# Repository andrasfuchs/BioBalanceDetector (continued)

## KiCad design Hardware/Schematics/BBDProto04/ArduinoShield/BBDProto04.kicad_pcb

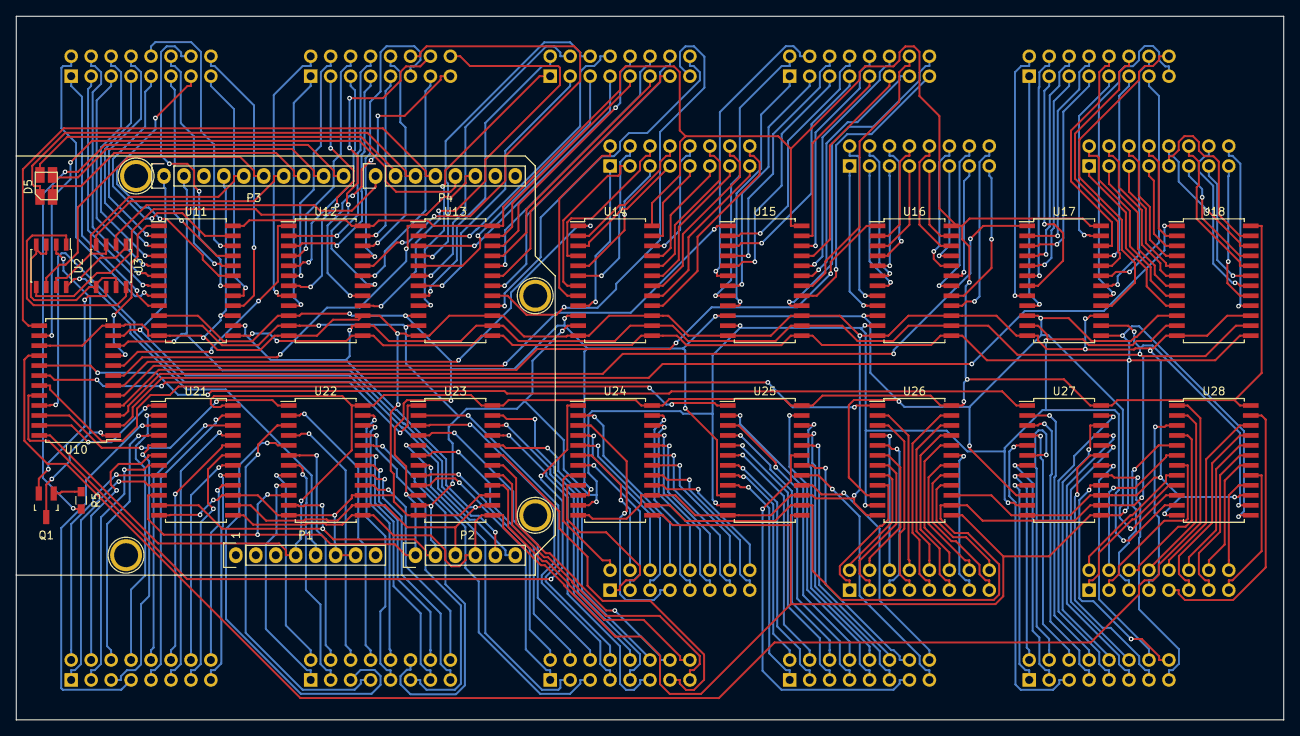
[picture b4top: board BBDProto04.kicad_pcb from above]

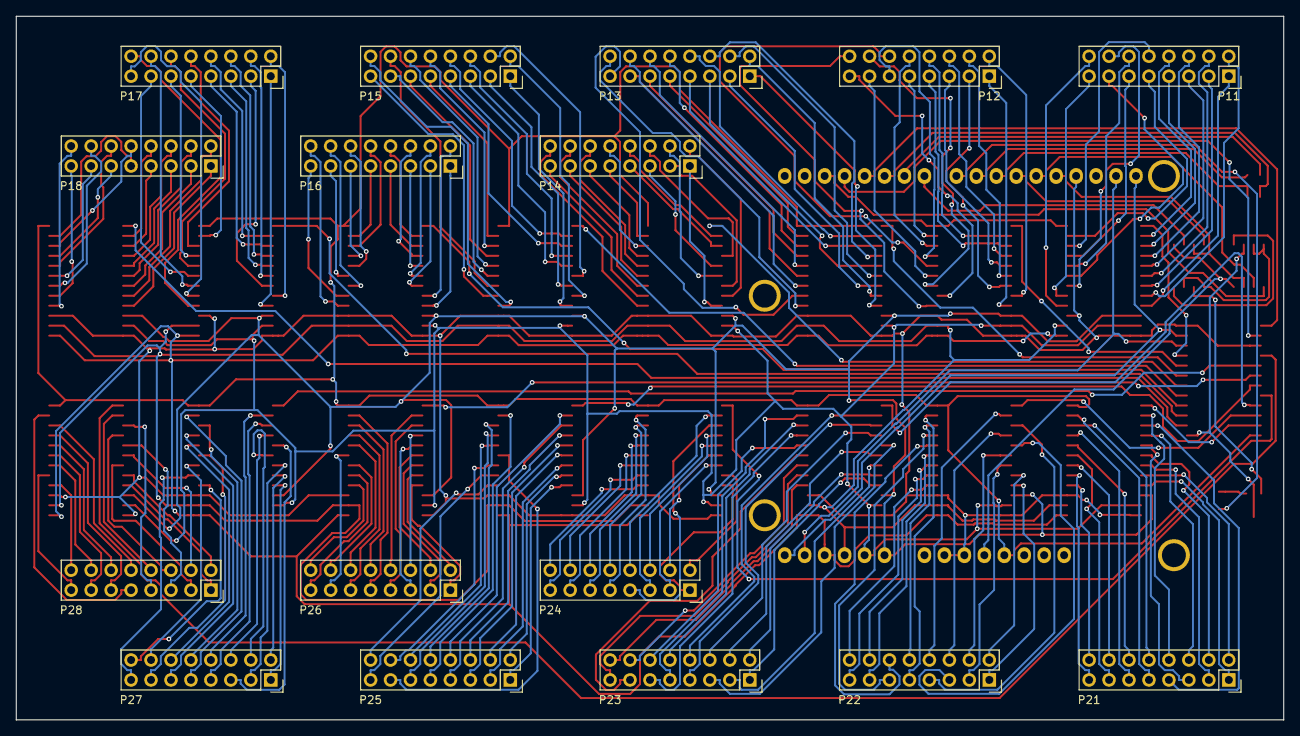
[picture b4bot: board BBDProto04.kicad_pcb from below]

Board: 2 copper layers, 161.3 x 89.5 mm, 46 parts (16 on the bottom side), 298 nets.

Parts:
D5: LED_RCBG; LED_3528-PLCC4
P1: Power; Socket_Strip_Arduino_1x08
P2: Analog; Socket_Strip_Arduino_1x06
P3: Digital; Socket_Strip_Arduino_1x10
P4: Digital; Socket_Strip_Arduino_1x08
P5, P6, P7, P8: CONN_1; Arduino_1pin
P11, P12, P13, P14, P15, P16, P17, P18, P21, P22, P23, P24, P25, P26, P27, P28: CONN_02X08; Socket_Strip_Straight_2x08
Q1: Q_NPN_BCE; SOT-23_Handsoldering
R5: 1k; R_0603_HandSoldering
U2: LTC1864; SOIC-8_3.9x4.9mm_Pitch1.27mm
U3: MCP4822; SOIC-8_3.9x4.9mm_Pitch1.27mm
U10, U11, U12, U13, U14, U15, U16, U17, U18, U21, U22, U23, U24, U25, U26, U27, U28: CD74HC4067; SOIC-24_7.5x15.4mm_Pitch1.27mm

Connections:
/2: P4.6, U2.5
/3(**): P4.5, U10.14
/4: P4.4, U10.13
/5(**): D5.1, P4.3
/6(**): D5.4, P4.2
/7: P4.1, U3.2
/8: P3.10, R5.2
/9(**): D5.3, P3.9
/10(**/SS): D5.2, P3.8
/11(**/MOSI): P3.7, U3.4
/12(MISO): P3.6, U2.6
/13(SCK): P3.5, U2.7, U3.3
/+3.3V: P1.4, U10.24, U11.24, U12.24, U13.24, U14.24, U15.24, U16.24, U17.24, U18.24, U21.24, U22.24, U23.24, U24.24, U25.24, U26.24, U27.24, U28.24
/+5.0V: P1.5, U2.8, U3.1
/A0: P2.1, U11.10, U12.10, U13.10, U14.10, U15.10, U16.10, U17.10, U18.10, U21.10, U22.10, U23.10, U24.10, U25.10, U26.10, U27.10, U28.10
/A1: P2.2, U11.11, U12.11, U13.11, U14.11, U15.11, U16.11, U17.11, U18.11, U21.11, U22.11, U23.11, U24.11, U25.11, U26.11, U27.11, U28.11
/A2: P2.3, U11.14, U12.14, U13.14, U14.14, U15.14, U16.14, U17.14, U18.14, U21.14, U22.14, U23.14, U24.14, U25.14, U26.14, U27.14, U28.14
/A3: P2.4, U11.13, U12.13, U13.13, U14.13, U15.13, U16.13, U17.13, U18.13, U21.13, U22.13, U23.13, U24.13, U25.13, U26.13, U27.13, U28.13
/A4(SDA): P2.5, P3.2, U10.10
/A5(SCL): P2.6, P3.1, U10.11
/ADC-VREF: U2.1, U3.8
/DAC-MULTIPLEXER-OUTPUT: Q1.2, U3.6
/MULTIPLEXER-INPUT: Q1.3, U2.2, U10.1
GND: P1.6, P1.7, P3.4, U10.12, U10.15, U11.12, U11.15, U12.12, U12.15, U13.12, U13.15, U14.12, U14.15, U15.12, U15.15, U16.12, U16.15, U17.12, U17.15, U18.12, U18.15, U21.12, U21.15, U22.12, U22.15, U23.12, U23.15, U24.12, U24.15, U25.12, U25.15, U26.12, U26.15, U27.12, U27.15, U28.12, U28.15
unnamed: P11.1, U11.9
unnamed: P11.2, U11.8
unnamed: P11.3, U11.7
unnamed: P11.4, U11.6
unnamed: P11.5, U11.5
unnamed: P11.6, U11.4
unnamed: P11.7, U11.3
unnamed: P11.8, U11.2
unnamed: P11.9, U11.23
unnamed: P11.10, U11.22
unnamed: P11.11, U11.21
unnamed: P11.12, U11.20
unnamed: P11.13, U11.19
unnamed: P11.14, U11.18
unnamed: P11.15, U11.17
unnamed: P11.16, U11.16
unnamed: P12.1, U12.9
unnamed: P12.2, U12.8
unnamed: P12.3, U12.7
unnamed: P12.4, U12.6
unnamed: P12.5, U12.5
unnamed: P12.6, U12.4
unnamed: P12.7, U12.3
unnamed: P12.8, U12.2
unnamed: P12.9, U12.23
unnamed: P12.10, U12.22
unnamed: P12.11, U12.21
unnamed: P12.12, U12.20
unnamed: P12.13, U12.19
unnamed: P12.14, U12.18
unnamed: P12.15, U12.17
unnamed: P12.16, U12.16
unnamed: P13.1, U13.9
unnamed: P13.2, U13.8
unnamed: P13.3, U13.7
unnamed: P13.4, U13.6
unnamed: P13.5, U13.5
unnamed: P13.6, U13.4
unnamed: P13.7, U13.3
unnamed: P13.8, U13.2
unnamed: P13.9, U13.23
unnamed: P13.10, U13.22
unnamed: P13.11, U13.21
unnamed: P13.12, U13.20
unnamed: P13.13, U13.19
unnamed: P13.14, U13.18
unnamed: P13.15, U13.17
unnamed: P13.16, U13.16
unnamed: P14.1, U14.9
unnamed: P14.2, U14.8
unnamed: P14.3, U14.7
unnamed: P14.4, U14.6
unnamed: P14.5, U14.5
unnamed: P14.6, U14.4
unnamed: P14.7, U14.3
unnamed: P14.8, U14.2
unnamed: P14.9, U14.23
unnamed: P14.10, U14.22
unnamed: P14.11, U14.21
unnamed: P14.12, U14.20
unnamed: P14.13, U14.19
unnamed: P14.14, U14.18
unnamed: P14.15, U14.17
unnamed: P14.16, U14.16
unnamed: P15.1, U15.9
unnamed: P15.2, U15.8
unnamed: P15.3, U15.7
unnamed: P15.4, U15.6
unnamed: P15.5, U15.5
unnamed: P15.6, U15.4
unnamed: P15.7, U15.3
unnamed: P15.8, U15.2
unnamed: P15.9, U15.23
unnamed: P15.10, U15.22
unnamed: P15.11, U15.21
unnamed: P15.12, U15.20
unnamed: P15.13, U15.19
unnamed: P15.14, U15.18
unnamed: P15.15, U15.17
unnamed: P15.16, U15.16
unnamed: P16.1, U16.9
unnamed: P16.2, U16.8
unnamed: P16.3, U16.7
unnamed: P16.4, U16.6
unnamed: P16.5, U16.5
unnamed: P16.6, U16.4
unnamed: P16.7, U16.3
unnamed: P16.8, U16.2
unnamed: P16.9, U16.23
unnamed: P16.10, U16.22
unnamed: P16.11, U16.21
unnamed: P16.12, U16.20
unnamed: P16.13, U16.19
unnamed: P16.14, U16.18
unnamed: P16.15, U16.17
unnamed: P16.16, U16.16
unnamed: P17.1, U17.9
unnamed: P17.2, U17.8
unnamed: P17.3, U17.7
unnamed: P17.4, U17.6
unnamed: P17.5, U17.5
unnamed: P17.6, U17.4
unnamed: P17.7, U17.3
unnamed: P17.8, U17.2
unnamed: P17.9, U17.23
unnamed: P17.10, U17.22
unnamed: P17.11, U17.21
unnamed: P17.12, U17.20
unnamed: P17.13, U17.19
unnamed: P17.14, U17.18
unnamed: P17.15, U17.17
unnamed: P17.16, U17.16
unnamed: P18.1, U18.9
unnamed: P18.2, U18.8
unnamed: P18.3, U18.7
unnamed: P18.4, U18.6
unnamed: P18.5, U18.5
unnamed: P18.6, U18.4
unnamed: P18.7, U18.3
unnamed: P18.8, U18.2
unnamed: P18.9, U18.23
unnamed: P18.10, U18.22
unnamed: P18.11, U18.21
unnamed: P18.12, U18.20
unnamed: P18.13, U18.19
unnamed: P18.14, U18.18
unnamed: P18.15, U18.17
unnamed: P18.16, U18.16
unnamed: P21.1, U21.9
unnamed: P21.2, U21.8
unnamed: P21.3, U21.7
unnamed: P21.4, U21.6
unnamed: P21.5, U21.5
unnamed: P21.6, U21.4
unnamed: P21.7, U21.3
unnamed: P21.8, U21.2
unnamed: P21.9, U21.23
unnamed: P21.10, U21.22
unnamed: P21.11, U21.21
unnamed: P21.12, U21.20
unnamed: P21.13, U21.19
unnamed: P21.14, U21.18
unnamed: P21.15, U21.17
unnamed: P21.16, U21.16
unnamed: P22.1, U22.9
unnamed: P22.2, U22.8
unnamed: P22.3, U22.7
unnamed: P22.4, U22.6
unnamed: P22.5, U22.5
unnamed: P22.6, U22.4
unnamed: P22.7, U22.3
unnamed: P22.8, U22.2
unnamed: P22.9, U22.23
unnamed: P22.10, U22.22
unnamed: P22.11, U22.21
unnamed: P22.12, U22.20
unnamed: P22.13, U22.19
unnamed: P22.14, U22.18
unnamed: P22.15, U22.17
unnamed: P22.16, U22.16
unnamed: P23.1, U23.9
unnamed: P23.2, U23.8
unnamed: P23.3, U23.7
unnamed: P23.4, U23.6
unnamed: P23.5, U23.5
unnamed: P23.6, U23.4
unnamed: P23.7, U23.3
unnamed: P23.8, U23.2
unnamed: P23.9, U23.23
unnamed: P23.10, U23.22
unnamed: P23.11, U23.21
unnamed: P23.12, U23.20
unnamed: P23.13, U23.19
unnamed: P23.14, U23.18
unnamed: P23.15, U23.17
unnamed: P23.16, U23.16
unnamed: P24.1, U24.9
unnamed: P24.2, U24.8
unnamed: P24.3, U24.7
unnamed: P24.4, U24.6
unnamed: P24.5, U24.5
unnamed: P24.6, U24.4
unnamed: P24.7, U24.3
unnamed: P24.8, U24.2
unnamed: P24.9, U24.23
unnamed: P24.10, U24.22
unnamed: P24.11, U24.21
unnamed: P24.12, U24.20
unnamed: P24.13, U24.19
unnamed: P24.14, U24.18
unnamed: P24.15, U24.17
unnamed: P24.16, U24.16
unnamed: P25.1, U25.9
unnamed: P25.2, U25.8
unnamed: P25.3, U25.7
unnamed: P25.4, U25.6
unnamed: P25.5, U25.5
unnamed: P25.6, U25.4
unnamed: P25.7, U25.3
unnamed: P25.8, U25.2
unnamed: P25.9, U25.23
unnamed: P25.10, U25.22
unnamed: P25.11, U25.21
unnamed: P25.12, U25.20
unnamed: P25.13, U25.19
unnamed: P25.14, U25.18
unnamed: P25.15, U25.17
unnamed: P25.16, U25.16
unnamed: P26.1, U26.9
unnamed: P26.2, U26.8
unnamed: P26.3, U26.7
unnamed: P26.4, U26.6
unnamed: P26.5, U26.5
unnamed: P26.6, U26.4
unnamed: P26.7, U26.3
unnamed: P26.8, U26.2
unnamed: P26.9, U26.23
unnamed: P26.10, U26.22
unnamed: P26.11, U26.21
unnamed: P26.12, U26.20
unnamed: P26.13, U26.19
unnamed: P26.14, U26.18
unnamed: P26.15, U26.17
unnamed: P26.16, U26.16
unnamed: P27.1, U27.9
unnamed: P27.2, U27.8
unnamed: P27.3, U27.7
unnamed: P27.4, U27.6
unnamed: P27.5, U27.5
unnamed: P27.6, U27.4
unnamed: P27.7, U27.3
unnamed: P27.8, U27.2
unnamed: P27.9, U27.23
unnamed: P27.10, U27.22
unnamed: P27.11, U27.21
unnamed: P27.12, U27.20
unnamed: P27.13, U27.19
unnamed: P27.14, U27.18
unnamed: P27.15, U27.17
unnamed: P27.16, U27.16
unnamed: P28.1, U28.9
unnamed: P28.2, U28.8
unnamed: P28.3, U28.7
unnamed: P28.4, U28.6
unnamed: P28.5, U28.5
unnamed: P28.6, U28.4
unnamed: P28.7, U28.3
unnamed: P28.8, U28.2
unnamed: P28.9, U28.23
unnamed: P28.10, U28.22
unnamed: P28.11, U28.21
unnamed: P28.12, U28.20
unnamed: P28.13, U28.19
unnamed: P28.14, U28.18
unnamed: P28.15, U28.17
unnamed: P28.16, U28.16
unnamed: Q1.1, R5.1
unnamed: U2.3, U2.4, U3.5, U3.7
unnamed: U10.2, U18.1
unnamed: U10.3, U17.1
unnamed: U10.4, U16.1
unnamed: U10.5, U15.1
unnamed: U10.6, U14.1
unnamed: U10.7, U13.1
unnamed: U10.8, U12.1
unnamed: U10.9, U11.1
unnamed: U10.16, U28.1
unnamed: U10.17, U27.1
unnamed: U10.18, U26.1
unnamed: U10.19, U25.1
unnamed: U10.20, U24.1
unnamed: U10.21, U23.1
unnamed: U10.22, U22.1
unnamed: U10.23, U21.1

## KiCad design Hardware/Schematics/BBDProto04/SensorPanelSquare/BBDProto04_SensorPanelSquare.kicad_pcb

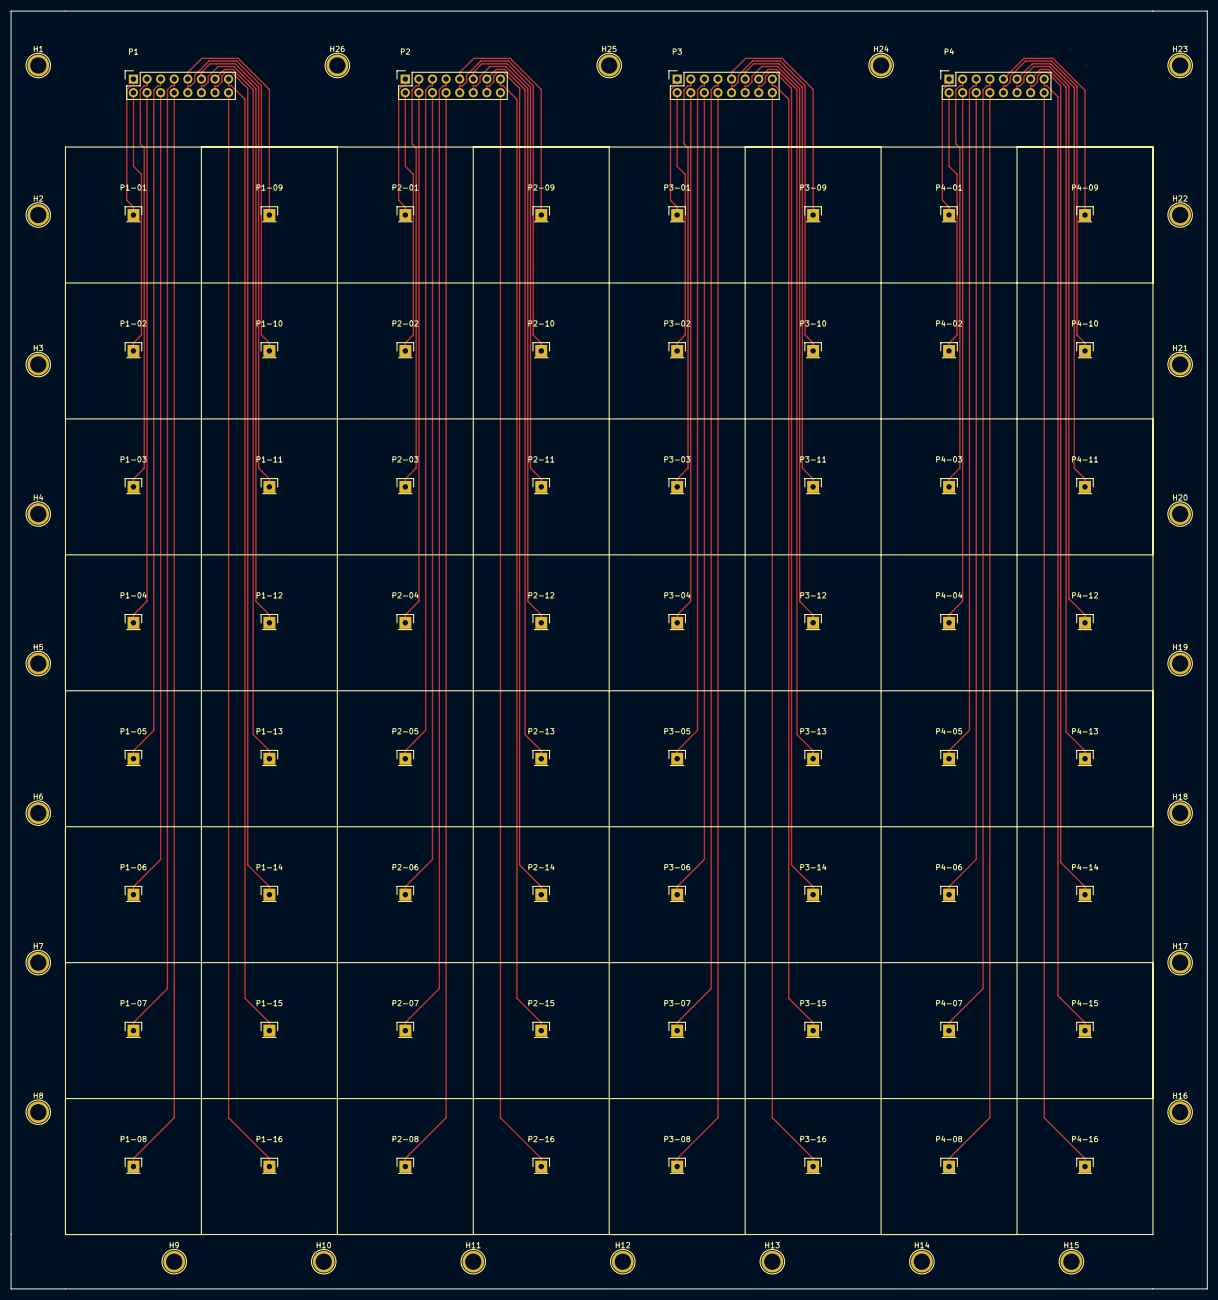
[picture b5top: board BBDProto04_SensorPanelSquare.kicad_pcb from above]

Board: 2 copper layers, 223.5 x 238.8 mm, 94 parts (0 on the bottom side), 64 nets.

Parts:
H1, H2, H3, H4, H5, H6, H7, H8, H9, H10, H11, H12, H13, H14, H15, H16, H17, H18, H19, H20, H21, H22, H23, H24, H25, H26: CONN_01X01; Arduino_1pin
P1, P2, P3, P4: CONN_02X08; Socket_Strip_Straight_2x08
P1-01, P1-02, P1-03, P1-04, P1-05, P1-06, P1-07, P1-08, P1-09, P1-10, P1-11, P1-12, P1-13, P1-14, P1-15, P1-16, P2-01, P2-02, P2-03, P2-04, P2-05, P2-06, P2-07, P2-08, P2-09, P2-10, P2-11, P2-12, P2-13, P2-14, P2-15, P2-16, P3-01, P3-02, P3-03, P3-04, P3-05, P3-06, P3-07, P3-08, P3-09, P3-10, P3-11, P3-12, P3-13, P3-14, P3-15, P3-16, P4-01, P4-02, P4-03, P4-04, P4-05, P4-06, P4-07, P4-08, P4-09, P4-10, P4-11, P4-12, P4-13, P4-14, P4-15, P4-16: CONN_01X01; Pin_Header_Straight_1x01

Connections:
unnamed: P1.1, P1-01.1
unnamed: P1.2, P1-02.1
unnamed: P1.3, P1-03.1
unnamed: P1.4, P1-04.1
unnamed: P1.5, P1-05.1
unnamed: P1.6, P1-06.1
unnamed: P1.7, P1-07.1
unnamed: P1.8, P1-08.1
unnamed: P1.9, P1-09.1
unnamed: P1.10, P1-10.1
unnamed: P1.11, P1-11.1
unnamed: P1.12, P1-12.1
unnamed: P1.13, P1-13.1
unnamed: P1.14, P1-14.1
unnamed: P1.15, P1-15.1
unnamed: P1.16, P1-16.1
unnamed: P2.1, P2-01.1
unnamed: P2.2, P2-02.1
unnamed: P2.3, P2-03.1
unnamed: P2.4, P2-04.1
unnamed: P2.5, P2-05.1
unnamed: P2.6, P2-06.1
unnamed: P2.7, P2-07.1
unnamed: P2.8, P2-08.1
unnamed: P2.9, P2-09.1
unnamed: P2.10, P2-10.1
unnamed: P2.11, P2-11.1
unnamed: P2.12, P2-12.1
unnamed: P2.13, P2-13.1
unnamed: P2.14, P2-14.1
unnamed: P2.15, P2-15.1
unnamed: P2.16, P2-16.1
unnamed: P3.1, P3-01.1
unnamed: P3.2, P3-02.1
unnamed: P3.3, P3-03.1
unnamed: P3.4, P3-04.1
unnamed: P3.5, P3-05.1
unnamed: P3.6, P3-06.1
unnamed: P3.7, P3-07.1
unnamed: P3.8, P3-08.1
unnamed: P3.9, P3-09.1
unnamed: P3.10, P3-10.1
unnamed: P3.11, P3-11.1
unnamed: P3.12, P3-12.1
unnamed: P3.13, P3-13.1
unnamed: P3.14, P3-14.1
unnamed: P3.15, P3-15.1
unnamed: P3.16, P3-16.1
unnamed: P4.1, P4-01.1
unnamed: P4.2, P4-02.1
unnamed: P4.3, P4-03.1
unnamed: P4.4, P4-04.1
unnamed: P4.5, P4-05.1
unnamed: P4.6, P4-06.1
unnamed: P4.7, P4-07.1
unnamed: P4.8, P4-08.1
unnamed: P4.9, P4-09.1
unnamed: P4.10, P4-10.1
unnamed: P4.11, P4-11.1
unnamed: P4.12, P4-12.1
unnamed: P4.13, P4-13.1
unnamed: P4.14, P4-14.1
unnamed: P4.15, P4-15.1
unnamed: P4.16, P4-16.1

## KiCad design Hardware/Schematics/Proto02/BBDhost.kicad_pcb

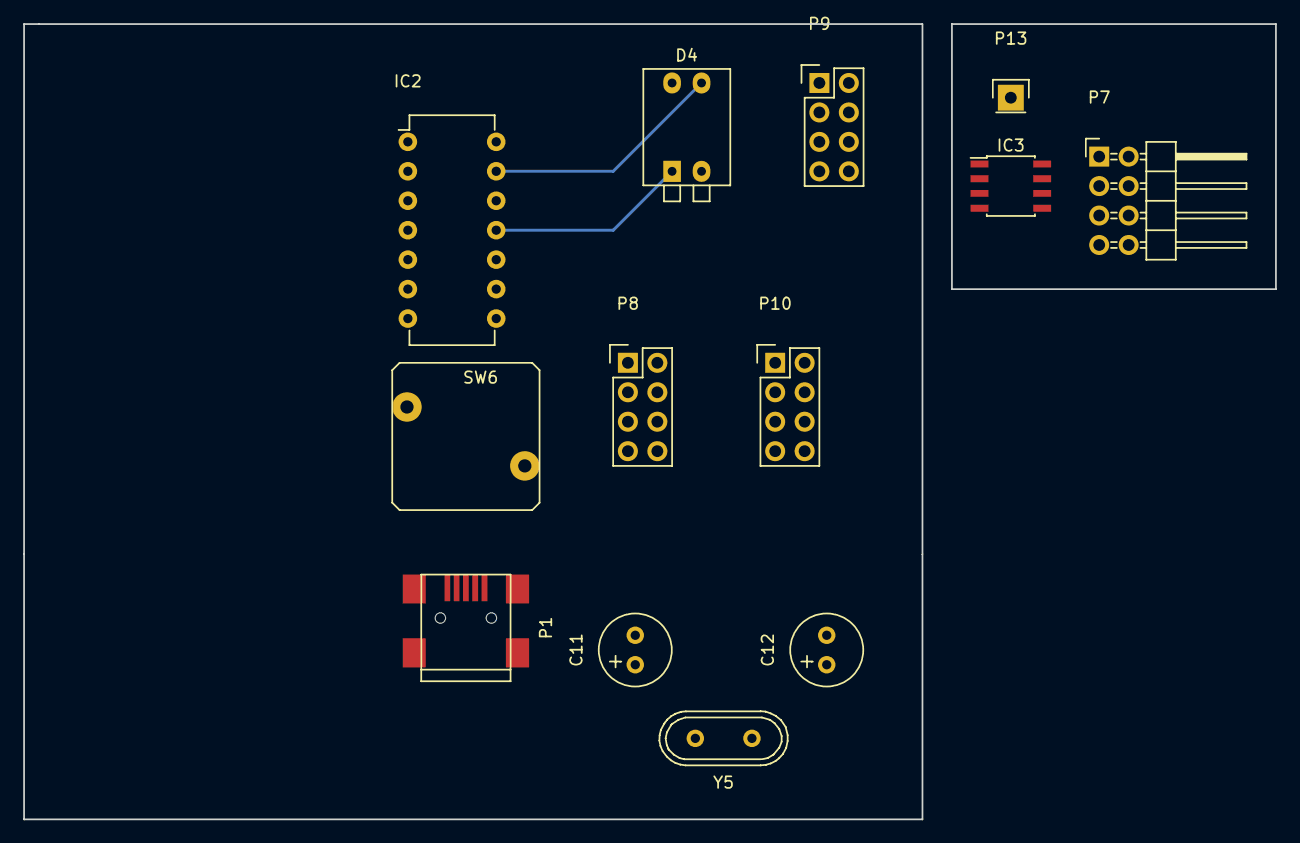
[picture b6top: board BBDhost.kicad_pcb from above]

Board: 2 copper layers, 107.9 x 68.6 mm, 13 parts (0 on the bottom side), 24 nets.

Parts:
C11, C12: 12-22pF; Elko_vert_11.2x6.3mm_RM2.5_CopperClear
D4: LED_RCBG; SW_DIP_x2_Piano
IC2: ATTINY84A-P; DIP-14_W7.62mm
IC3: ATTINY25-S; SOIC-8_3.9x4.9mm_Pitch1.27mm
P1: USB_OTG; USB_Mini-B
P7: DIL8; Pin_Header_Angled_2x04
P8, P9, P10: DIL8; Pin_Header_Straight_2x04
P13: SENSOR; Pin_Header_Straight_1x01
SW6: CHANGE MODE; SW_PUSH
Y5: 20 Mhz; Crystal_HC49-U_Vertical

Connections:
unnamed: C11.1, IC2.3, P8.3, P9.3, P10.3, Y5.2
unnamed: C11.2, C12.2, IC2.14, P1.5, P8.4, P9.4, P10.4
unnamed: C12.1, IC2.2, P8.2, P9.2, P10.2, Y5.1
unnamed: D4.1, IC2.11
unnamed: D4.2, IC2.10
unnamed: D4.3, IC2.13
unnamed: D4.4, IC2.12
unnamed: IC2.1, P1.1, P8.8, P9.8, P10.8, SW6.1
unnamed: IC2.4, P1.3
unnamed: IC2.5, P1.2
unnamed: IC2.6, SW6.2
unnamed: IC2.7, P10.6
unnamed: IC2.8, P8.5
unnamed: IC2.9, P8.7, P9.7, P10.7
unnamed: IC3.1, P13.1
unnamed: IC3.2, P7.2
unnamed: IC3.3, P7.3
unnamed: IC3.4, P7.4
unnamed: IC3.5, P7.5
unnamed: IC3.6, P7.6
unnamed: IC3.7, P7.7
unnamed: IC3.8, P7.8
unnamed: P8.6, P9.5
unnamed: P9.6, P10.5

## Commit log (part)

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2017-08-09 Changed the Target Framework to 4.7
    Changed the Target Framework to 4.7
2017-08-09 Added FFTW binaries
    Added FFTW binaries
2017-08-09 Removed Kitware Activiz.NET library references
    Removed Kitware Activiz.NET library references
2017-08-10 Added a new BBDInterface project
    Added a new BBDInterface project. This one is only temporary until the
    ASP.NET Core 2.0 MVC stabilizes
2017-08-13 Fixed an issue with ASF
    Fixed an issue with ASF
2017-08-13 Started the new schematic for Mercury-64
    Started the new schematic for Mercury-64
2017-08-30 Added a Wacom tablet as design suggestion
    Added a Wacom tablet as design suggestion
2017-08-30 Fixed the resolution of the photo of the Wacom tablet
    Fixed the resolution of the photo of the Wacom tablet
2017-08-30 Minor changes
    Minor changes
2017-09-07 Wiki backup
    Wiki backup
2017-09-07 Fixed some LCD texts and added some comments to the code
    Fixed some LCD texts and added some comments to the code
2017-09-07 15fps and 30fps GIFs of Mercury-16
    15fps and 30fps GIFs of Mercury-16
2017-09-07 Added the menu selection feature
    Added the menu selection feature
2017-09-14 Added the menu system
    Added the menu system to the LCD
2017-09-15 Upgraded ASF to 3.34.1
    Upgraded ASF to 3.34.1
2017-09-15 Restructured the ADC, LCD, USB, USART modules to separate files
    Restructured the ADC, LCD, USB, USART modules to separate files
2017-09-15 Made the testing easier with some code
    Made the testing easier with some code
2017-09-22 A few types of USBASP photo
    A few types of USBASP photo
2017-09-23 Added the KiCad Pcbnew generator project
    Added the KiCad Pcbnew generator project. This generates the different
    antennas on the flat detector panel's KiCad file.
2017-09-25 FlatPanelDetector and its generator
    FlatPanelDetector and its generator
2017-10-04 Fabrication files for the new flat panel detector
    Fabrication files for the new flat panel detector
2017-11-25 Changed the device GUID
    Changed the device GUID for Mr. Pepper
2017-11-25 Source code restructuring
    Source code restructuring and prepared for Goertzel algorithm implementation
2017-12-01 Added support for the float-based packets in the firmware
    Added support for the float-based packets in the firmware
2017-12-01 Added support for Goertzel packets
    Added support for Goertzel packets
2017-12-02 Reduced the heartbeat packets by a factor of 1000
    Reduced the heartbeat packets by a factor of 1000
2017-12-02 Refactored the USB/USART data sending method
    Refactored the USB/USART data sending method
2017-12-06 Settings struct upload
    Settings get requested and received by the driver from Mercury-16, modified by the driver and sent it back to Mercury.
2018-03-17 Updated readme
    Updated readme
2018-03-17 Added the measurements at KIBU
    Added the measurements at KIBU
2018-03-17 Sierpinski Gasket reseach paper
    Sierpinski Gasket reseach paper
2018-03-17 Added the fractal triangle antenna and made the drill holes bigger
    Added the fractal triangle antenna and made the drill holes bigger
2018-03-26 Added new photos of the Proto#5 Flat Panel Detector rev B
    Added new photos of the Proto#5 Flat Panel Detector rev B
2018-04-05 Photos of KIBU Lab
    Photos of KIBU Lab
2018-04-05 KIBU measurements
    KIBU measurements
2018-04-05 Switched the GUID back to the one on Mr. Pepper
    Switched the GUID back to the one on Mr. Pepper
2018-04-09 GitHub wiki backup
    GitHub wiki backup
2018-04-10 Fractal antenna documents
    Fractal antenna documents
2018-04-10 Raspberry Pi 3 B+ photo
    Raspberry Pi 3 B+ photo
2018-04-26 Input BizDev documents
2018-04-26 Fractal antenna designs
    Fractal antenna designs
2018-04-26 Added the older ATSAME70Q21 datasheet
    Added the older ATSAME70Q21 datasheet which has the correct 144-LQPF pin numbers
2018-04-27 Added datasheets and schematics of AD7616 EVAL board
    Added datasheets and schematics of AD7616 EVAL board
2018-04-27 Added Cell Slave capacitors
    Added Cell Slave capacitors
2018-04-27 Added ADG715 switch array
    Added ADG715 switch array
2018-04-28 Merkaba antennas
    Merkaba antennas
2018-05-02 Added a 5th cell-slave
    Added a 5th cell-slave
2018-05-11 Updated the AD7616 and its Cell Slave schematics
    Updated the AD7616 and its Cell Slave schematics
2018-05-11 Venus-256 RevA PCB render
    Venus-256 RevA PCB render
2018-05-25 Added the half of the fractal antennas
2018-05-25 Fixed many rules check errors and changed the footprint of test points
2018-05-28 Moved the TPS22993
    Moved the TPS22993
2018-05-28 Added jumpers to TPS22993
2018-05-28 Added the SensorLine net class
2018-05-28 Fixed the triangle nets
2018-05-28 Switched around the ADC channels to make the PCB simpler
2018-05-28 Wired the U401 sensors
2018-12-04 Updated gitignore
2018-12-04 Updated a few wire tracks
2018-12-04 Created the batch file for FreeRouting (KiCad auto-router extension)
2018-12-05 Removed all tracks from the PCB
2018-12-05 Fixed the nets connected to 16 pads
2018-12-06 Expanded the sensors by adding an extra 0.65mm gap between them and rearraged the MCUs a little
2018-12-06 Modified the script a little (with the help of @attila)
2018-12-06 Revert "Connected the sensors manually"
    This reverts commit 920ffef15f235d024d89dcae21abf078b3e216eb.
2018-12-06 Removed a few tracks
2018-12-07 Wired one of the ADCs manually
2018-12-07 Rearranged the ADCs
2018-12-07 Routed U601 manually
2018-12-08 Rearranged the components again
2018-12-20 Placed and partially wired one ATSAME70Q21
2018-12-20 Added the PowerGround net class
2018-12-20 All sensors are connected
2018-12-20 Shrinked the PCB a little
2018-12-20 Connected the power lines to the MCUs
2018-12-20 Wired the power lines and some other signals
2018-12-22 Updated the signature frequency script
2019-01-15 Updated AD2 tests
2019-03-29 Raspberry Pi Python samples
2019-03-29 Spooky2 measurements
2019-03-29 Venus-256 autorouter file
2019-05-15 Added Spooky2 Lyme protocol
2019-05-15 Updated a few instructions for Raspberry Pi
2019-05-15 Two batch files to make remote building for Raspberry Pi easier
2019-05-15 Added PDF: An Electric Field Detector for high-performance measurements of the electric ﬁeld in the ionosphere
2019-05-15 Added the video file of the Bemer 10 experiment
2019-05-20 Investigated the I2C us of Raspberry Pi
2019-05-20 Modified the logic to pattern generation
2019-05-20 Added LED blinking for extra strong fields
2019-05-20 Fixed the sounds frequencies
2019-05-21 Test the SPI of AD7616 with Analog Discovery 2
2019-05-26 Added the Sleep logging experiment
2019-05-26 Updated the aquisition file naming logic
2019-05-26 Removed some dummy data
2019-05-27 Modified the sleep logger script with the help of attila@Digilent
2019-05-27 Added a few meditations and their intructions
2019-05-27 Refined the real-time algorithm
2019-06-22 Website
2019-06-22 Sleep logging instrunctions update
2019-07-07 Branding: added blog logo files
2019-07-07 Update configuration to match USB device identifier for "Sheldon"
2019-07-21 Logo at different resolutions
2019-07-21 I did a few more experiments with water and beer
2019-10-14 Logos at different resolutions
2019-10-14 Fluid impedance profiles experiment
2019-10-14 New website version
2019-10-14 Bump mixin-deep from 1.3.1 to 1.3.2 in /Website/Version_2
    Bumps [mixin-deep](https://github.com/jonschlinkert/mixin-deep) from 1.3.1 to 1.3.2.
    - [Release notes](https://github.com/jonschlinkert/mixin-deep/releases)
    - [Commits](https://github.com/jonschlinkert/mixin-deep/compare/1.3.1...1.3.2)
2019-10-29 Fluid impedance results as PNG pictures
2019-11-22 Copied the pictures of the blog
2019-12-18 Added the new experiments (47-54)
2020-01-02 Highlighted articles by Peter Grandics
2020-01-23 Updated the KiCad cache of Venus-256
2020-01-23 Set footprints
2020-01-24 Designed the first version of Mars-64's PCB
2020-01-25 Updated the autorounter
2020-01-25 Added the custom Pmod footprints to the project's library
2020-01-25 Moved U201 and U202 a little
2020-01-31 Changed the PCB size to 51x61mm
2020-01-31 Updated the ADG731 symbol
2020-02-01 Autorouter files
2020-02-01 Added a list of useful PCB fabrication and components providers.
2020-02-11 Recompiled freerouting and its test files
2020-02-11 Updated the npm packages
    https://stackoverflow.com/questions/16073603/how-do-i-update-each-dependency-in-package-json-to-the-latest-version
2020-02-13 Changed the position of the Pmod pads
2020-02-13 Moved the older autorouter files into -revA folder
2020-02-13 Added the autorouter batch file to rev B
2020-02-13 Completed the routing of Mars-64 rev B
2020-02-16 Created a Raspberry Pi .NET Core publisher PowerShell script
2020-02-28 Generated PDF and DSN files for Eagle compatibility
2020-02-28 Added a VSS jumper
2020-02-28 Removed some unnacessary files
2020-02-28 Removed all the tracks and kept the locked vias only
2020-02-28 Prepared the files for autorouting
2020-02-28 Generated the fabrication files for Mars-64 Rev. C
2020-02-29 Connected the AGND to the fill zone
2020-03-01 Completed the autorouting for the U101 rotations
2020-03-01 Added the 2-layer version
2020-03-10 Added a GNURadio research/settings paper
2020-03-10 Added the AdcValue class and its threadsafe collection
2020-03-22 Updated the year in the website's footer
2020-03-22 Run another wiring test with freerouting
2020-03-22 Moved the files around to reflect the namespace changes
2020-03-25 Changed a few things after reading the "conventions for devices APIs"
2020-03-25 Removed an incorrent XML comment for a non-existent parameter
2020-05-05 Made new measurements with AD7193
2020-05-05 Fixed the connection problem of the UDP sinks
2020-05-10 Fixed a few bugs on the PCB and changed the revision from D to E
2020-05-10 Fixed the footprints of PmodF and PmodM, and removed the routed tracks
2020-05-10 Finished the routing for Mars-64 rev. E
2020-05-10 Unhid the In1.Cu layer
2020-05-10 Added some design elemets to the board
2020-05-16 Added the autorouter results from DeepPCB
2020-05-16 Updated the 2-layer PCB, preprared it for manufacturing
2020-05-16 Added the 3D models for the connectors
2020-07-09 Run the 'npm audit fix' command
2020-10-04 Added the rpi_ad7606 repo to the RaspberryPi.Python3 folder
2020-12-22 updated the modules
2021-01-07 Add C# Sleep Logger project
2021-01-07 Fix the DllImport reference to the DWF libary binary
2021-01-11 Add text to the PNG export
2021-01-12 Add JSON configuration file support and logging
2021-01-13 Fix the path combination
2021-01-13 Add Postprocessing.Enabled switch into the config file
2021-01-13 Add reinitialization logic
2021-01-14 Add video generation
2021-01-16 Fix the sample rate bug
2021-01-17 Fix the FFT path bug
2021-01-18 Set magnitude threshold to 0
2021-01-18 Extract the version string
2021-01-20 Change the AD2 configuration to the 2nd setting with 16k analog-in samples
2021-01-20 Lower the sampling rate to match the Raspberry Pi
2021-01-20 Change the filename structure
2021-01-22 Add chart colorization and fft resampling
2021-01-22 Add GenerateMLCSV method
2021-01-25 Move the SleepLogger into the software folder
2021-01-25 MinimumAvailableFreeSpace check update
2021-01-30 Add audio device listing
2021-02-02 Add error handling for the audio recording
2021-02-03 Change audio recording command lines
2021-02-03 Calculate audio capture time dynamically
2021-02-06 Refactor the audio encoding
2021-02-09 Upload photos of proto 08
2021-05-07 Bump ua-parser-js from 0.7.23 to 0.7.28 in /Website/Version_2
    Bumps [ua-parser-js](https://github.com/faisalman/ua-parser-js) from 0.7.23 to 0.7.28.
    - [Release notes](https://github.com/faisalman/ua-parser-js/releases)
    - [Commits](https://github.com/faisalman/ua-parser-js/compare/0.7.23...0.7.28)
2021-05-11 Bump hosted-git-info from 2.7.1 to 2.8.9 in /Website/Version_2
    Bumps [hosted-git-info](https://github.com/npm/hosted-git-info) from 2.7.1 to 2.8.9.
    - [Release notes](https://github.com/npm/hosted-git-info/releases)
    - [Changelog](https://github.com/npm/hosted-git-info/blob/v2.8.9/CHANGELOG.md)
    - [Commits](https://github.com/npm/hosted-git-info/compare/v2.7.1...v2.8.9)
